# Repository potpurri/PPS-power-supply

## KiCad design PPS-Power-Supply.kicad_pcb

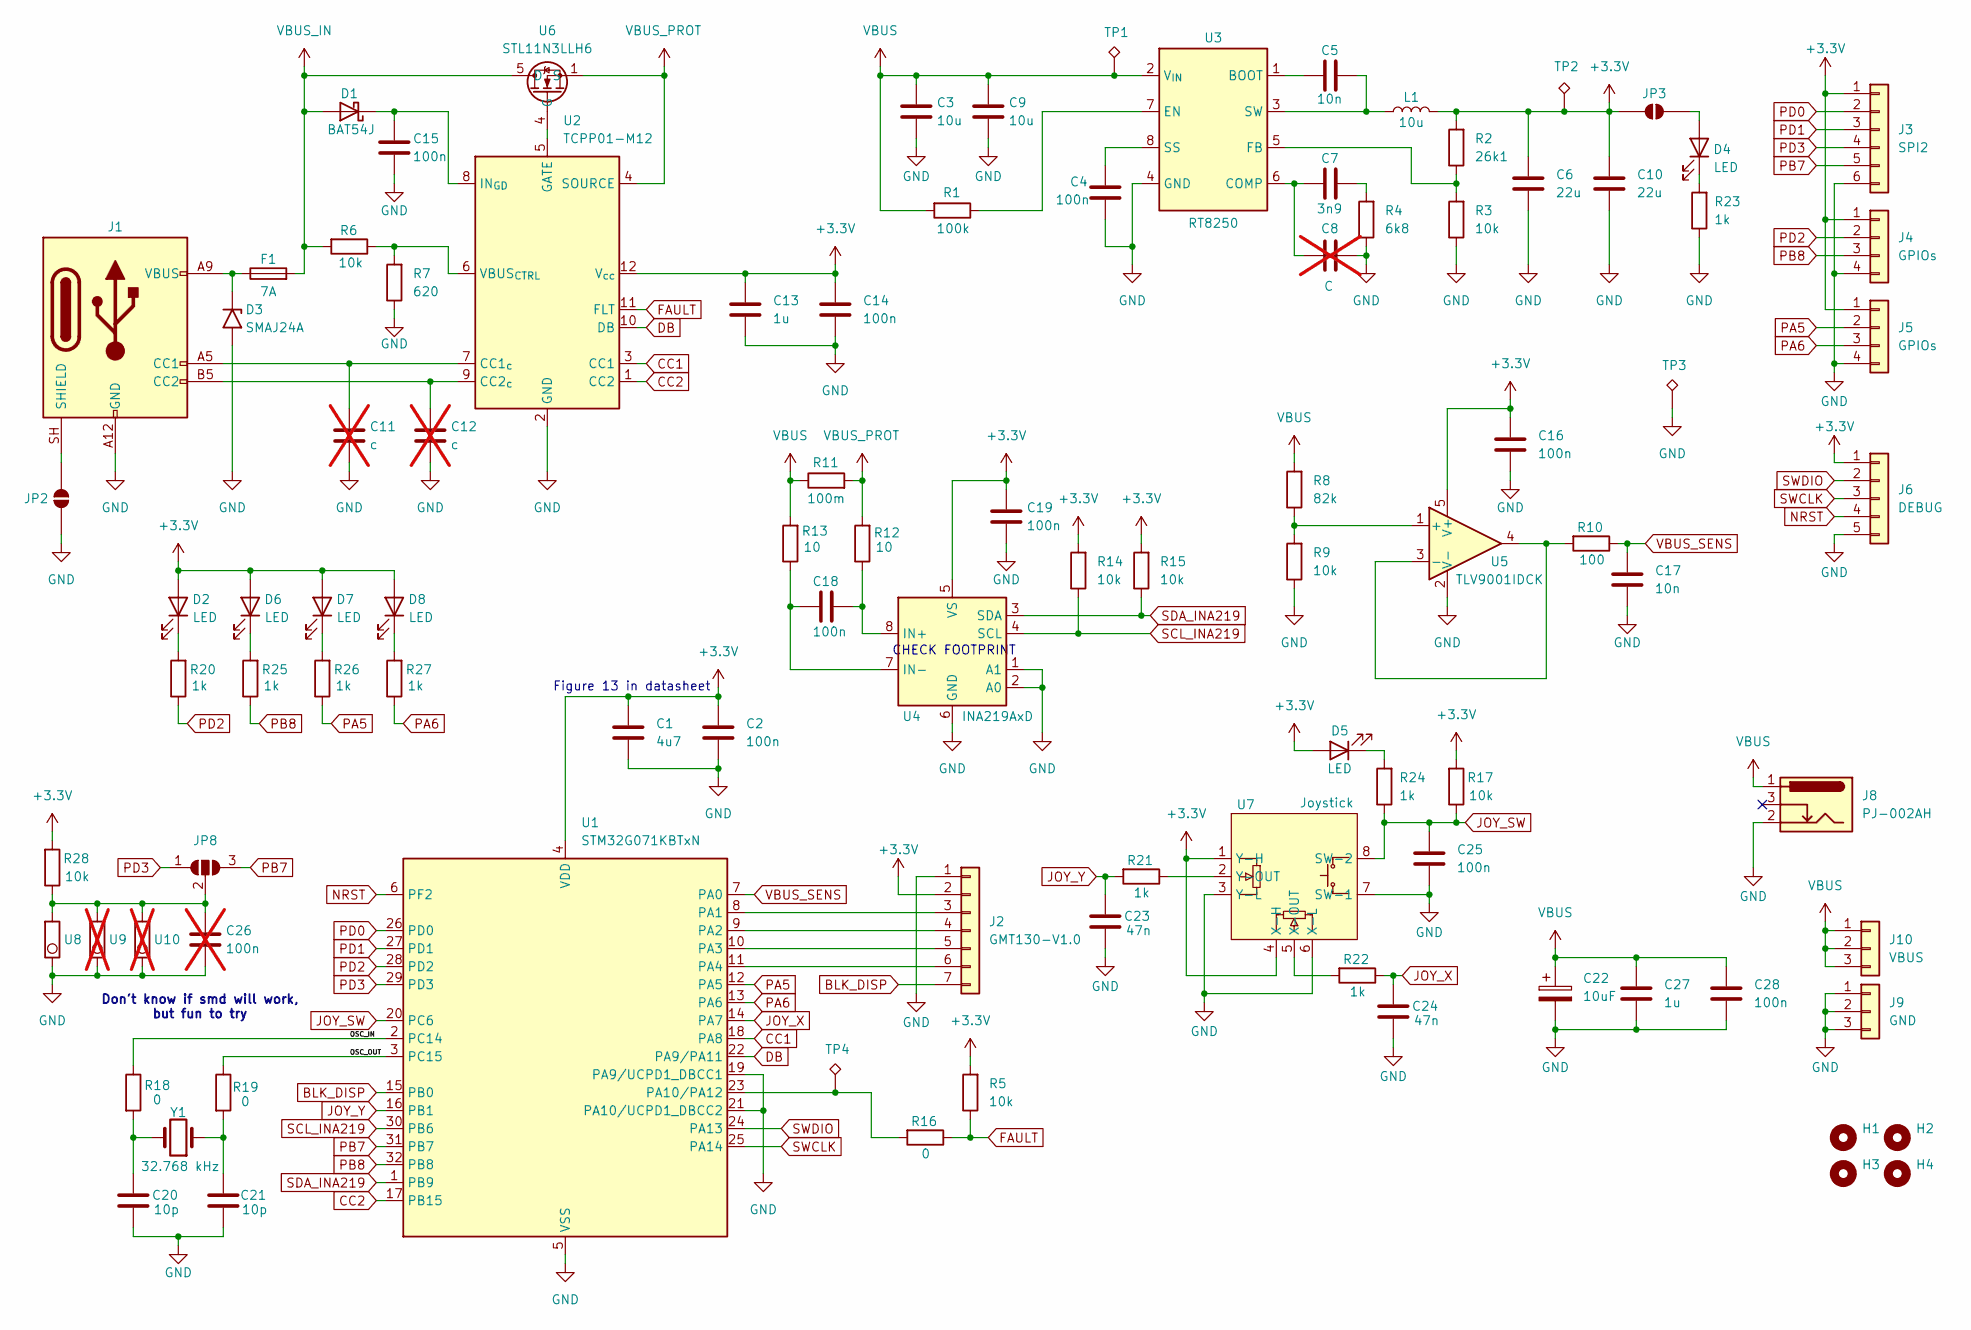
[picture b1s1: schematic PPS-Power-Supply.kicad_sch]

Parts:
C1: 4u7; C_0805_2012Metric
C2, C4, C14, C15, C16, C18, C19, C25, C28: 100n; C_0603_1608Metric
C3, C9: 10u; C_1206_3216Metric
C5, C17: 10n; C_0603_1608Metric
C6, C10: 22u; C_1206_3216Metric
C7: 3n9; C_0603_1608Metric
C8: C; C_0603_1608Metric; not fitted
C11, C12: c; C_0603_1608Metric; not fitted
C13, C27: 1u; C_0805_2012Metric
C20, C21: 10p; C_0603_1608Metric
C22: 10uF; CP_Elec_5x5.3
C23, C24: 47n; C_0603_1608Metric
C26: 100n; C_0603_1608Metric; not fitted
D1: BAT54J; D_SOD-323F
D2, D4, D5, D6, D7, D8: LED; LED_0805_2012Metric
D3: SMAJ24A; D_SMB
F1: 7A; Fuse_1206_3216Metric
H1, H2, H3, H4: MountingHole; MountingHole_3.2mm_M3_DIN965_Pad_TopBottom
J1: USB_C_Receptacle_PowerOnly_6P; USB_C_Receptacle_HRO_TYPE-C-31-M-17
J2: GMT130-V1.0; PinHeader_1x07_P2.54mm_Vertical
J3: SPI2; PinHeader_1x06_P2.54mm_Vertical
J4, J5: GPIOs; PinHeader_1x04_P2.54mm_Vertical
J6: DEBUG; PinHeader_1x05_P2.54mm_Vertical
J8: PJ-002AH; BarrelJack_GCT_DCJ200-10-A_Horizontal
J9: GND; PinHeader_1x03_P2.54mm_Vertical
J10: VBUS; PinHeader_1x03_P2.54mm_Vertical
JP2, JP3: SolderJumper_2_Open; SolderJumper-2_P1.3mm_Open_RoundedPad1.0x1.5mm
JP8: SolderJumper_3_Open; SolderJumper-3_P1.3mm_Open_RoundedPad1.0x1.5mm
L1: 10u; L_APV_ANR5020
R1: 100k; R_0603_1608Metric
R2: 26k1; R_0603_1608Metric
R3, R5, R6, R9, R14, R15, R17, R28: 10k; R_0603_1608Metric
R4: 6k8; R_0603_1608Metric
R7: 620; R_0603_1608Metric
R8: 82k; R_0603_1608Metric
R10: 100; R_0603_1608Metric
R11: 100m; R_2512_6332Metric
R12, R13: 10; R_0603_1608Metric
R16, R18, R19: 0; R_0805_2012Metric
R20, R21, R22, R23, R24, R25, R26, R27: 1k; R_0603_1608Metric
TP1, TP2, TP3, TP4: TestPoint_Alt; TestPoint_Pad_D1.0mm
U1: STM32G071KBTxN; LQFP-32_7x7mm_P0.8mm
U2: TCPP01-M12; QFN-12-1EP_3x3mm_P0.5mm_EP1.45x1.45mm
U3: RT8250; Texas_HSOP-8-1EP_3.9x4.9mm_P1.27mm
U4: INA219AxD; SOIC-8_3.9x4.9mm_P1.27mm
U5: TLV9001IDCK; SOT-353_SC-70-5
U6: STL11N3LLH6; POWERFLAT-3p3X3p3_STM
U7: Joystick
U8: R_Axial_DIN0411_L9.9mm_D3.6mm_P15.24mm_Horizontal
U9, U10: L_1210_3225Metric; not fitted
Y1: 32.768 kHz; Crystal_SMD_3215-2Pin_3.2x1.5mm

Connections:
+3.3V: C1.1, C2.1, C6.1, C10.1, C13.1, C14.1, C16.1, C19.1, D2.2 (A), D5.2 (A), D6.2 (A), D7.2 (A), D8.2 (A), J2.2, J3.1, J4.1, J5.1, J6.1, JP3.1 (A), L1.2, R2.2, R5.2, R14.2, R15.2, R17.2, R28.2, TP2.1 (1_1), U1.4 (VDD), U2.12 (V_{cc}), U4.5 (VS), U5.5 (V+), U7.1 (Y-H), U7.4 (X-H)
/OSC_IN: R18.1, U1.2 (PC14)
/OSC_OUT: R19.1, U1.3 (PC15)
BLK_DISP: J2.7, U1.15 (PB0)
CC1: U1.18 (PA8), U2.3 (CC1)
CC2: U1.17 (PB15), U2.1 (CC2)
DB: U1.22 (PA9/PA11), U2.10 (DB)
FAULT: R5.1, R16.1, U2.11 (FLT)
GND: C1.2, C2.2, C3.2, C4.2, C6.2, C8.2, C9.2, C10.2, C11.2, C12.2, C13.2, C14.2, C15.2, C16.2, C17.2, C19.2, C20.2, C21.2, C22.2, C23.2, C24.2, C25.2, C26.2, C27.2, C28.2, D3.2 (A2), J1.A12 (GND), J1.B12 (GND), J2.1, J3.6, J4.4, J5.4, J6.5, J8.2, J9.1, J9.2, J9.3, JP2.1 (A), R3.1, R4.1, R7.1, R9.1, R23.1, TP3.1 (1_1), U1.5 (VSS), U1.19 (PA9/UCPD1_DBCC1), U1.21 (PA10/UCPD1_DBCC2), U2.2 (GND), U2.13 (GND), U3.4 (GND), U3.9 (GND), U4.1 (A1), U4.2 (A0), U4.6 (GND), U5.2 (V-), U7.3 (Y-L), U7.6 (X-L), U7.7 (SW-1), U8., U8.1, U9., U9.1, U10., U10.1
JOY_SW: C25.1, R17.1, R24.1, U1.20 (PC6), U7.8 (SW-2)
JOY_X: C24.1, R22.1, U1.14 (PA7)
JOY_Y: C23.1, R21.2, U1.16 (PB1)
NRST: J6.4, U1.6 (PF2)
unnamed: C7.2, R4.2
unnamed: C20.1, R18.2, Y1.2
unnamed: C21.1, R19.2, Y1.1
unnamed: C15.1, D1.1 (K), U2.8 (IN_{GD})
unnamed: D2.1 (K), R20.2
unnamed: D3.1 (A1), F1.1, J1.A9 (VBUS), J1.B9 (VBUS)
unnamed: D4.2 (A), JP3.2 (B)
unnamed: D4.1 (K), R23.2
unnamed: D5.1 (K), R24.2
unnamed: D6.1 (K), R25.2
unnamed: D7.1 (K), R26.2
unnamed: D8.1 (K), R27.2
unnamed: C11.1, J1.A5 (CC1), U2.7 (CC1_{c})
unnamed: C12.1, J1.B5 (CC2), U2.9 (CC2_{c})
unnamed: J1.SH (SHIELD), JP2.2 (B)
unnamed: J2.3, U1.8 (PA1)
unnamed: J2.4, U1.9 (PA2)
unnamed: J2.5, U1.10 (PA3)
unnamed: J2.6, U1.11 (PA4)
unnamed: C26.1, JP8.2 (C), R28.1, U8., U8.2, U9., U9.2, U10., U10.2
unnamed: R16.2, TP4.1 (1_1), U1.23 (PA10/PA12)
unnamed: U2.5 (GATE), U6.4 (G)
unnamed: R6.1, R7.2, U2.6 (VBUS_{CTRL})
unnamed: C5.1, U3.1 (BOOT)
unnamed: C7.1, C8.1, U3.6 (COMP)
unnamed: R1.1, U3.7 (EN)
unnamed: R2.1, R3.2, U3.5 (FB)
unnamed: C4.1, U3.8 (SS)
unnamed: C5.2, L1.1, U3.3 (SW)
unnamed: C18.1, R12.1, U4.8 (IN+)
unnamed: C18.2, R13.1, U4.7 (IN-)
unnamed: R8.1, R9.2, U5.1 (+)
unnamed: R10.2, U5.3 (-), U5.4
unnamed: R22.2, U7.5 (X-OUT)
unnamed: R21.1, U7.2 (Y-OUT)
PA5: J5.2, R26.1, U1.12 (PA5)
PA6: J5.3, R27.1, U1.13 (PA6)
PB7: J3.5, JP8.3 (B), U1.31 (PB7)
PB8: J4.3, R25.1, U1.32 (PB8)
PD0: J3.2, U1.26 (PD0)
PD1: J3.3, U1.27 (PD1)
PD2: J4.2, R20.1, U1.28 (PD2)
PD3: J3.4, JP8.1 (A), U1.29 (PD3)
SCL_INA219: R14.1, U1.30 (PB6), U4.4 (SCL)
SDA_INA219: R15.1, U1.1 (PB9), U4.3 (SDA)
SWCLK: J6.3, U1.25 (PA14)
SWDIO: J6.2, U1.24 (PA13)
VBUS: C3.1, C9.1, C22.1, C27.1, C28.1, J8.1, J10.1, J10.2, J10.3, R1.2, R8.2, R11.1, R13.2, TP1.1 (1_1), U3.2 (V_{IN})
VBUS_IN: D1.2 (A), F1.2, R6.2, U6.5 (D), U6.6 (D), U6.7 (D), U6.8 (D)
VBUS_PROT: R11.2, R12.2, U2.4 (SOURCE), U6.1 (S), U6.2 (S), U6.3 (S)
VBUS_SENS: C17.1, R10.1, U1.7 (PA0)

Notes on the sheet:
Don't know if smd will work, but fun to try
CHECK FOOTPRINT
Figure 13 in datasheet

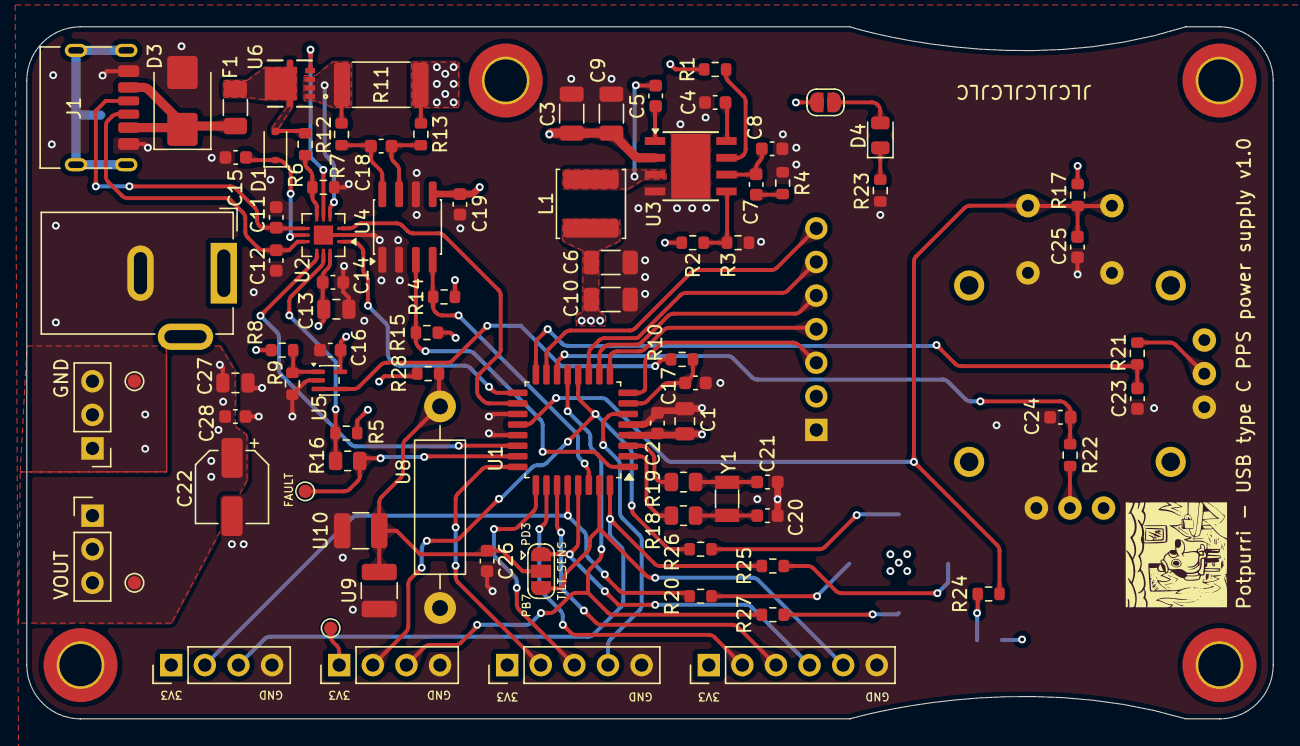
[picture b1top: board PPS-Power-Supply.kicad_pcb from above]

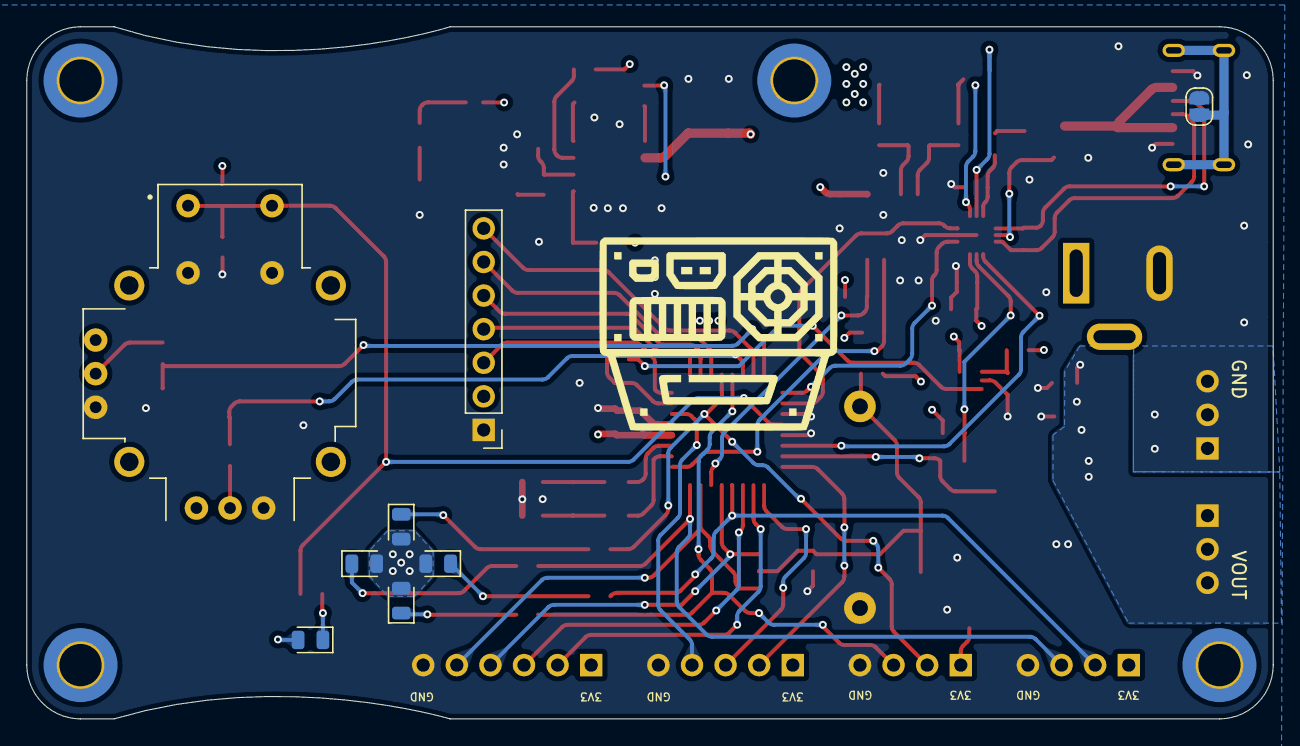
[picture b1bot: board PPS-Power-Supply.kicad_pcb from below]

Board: 4 copper layers, 94.2 x 52.3 mm, 97 parts (8 on the bottom side), 64 nets.

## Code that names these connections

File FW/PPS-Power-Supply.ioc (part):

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Mcu.Name=STM32G071K(8-B)TxN
Mcu.Package=LQFP32
Mcu.UserName=STM32G071KBTxN
PA0.GPIOParameters=GPIO_Label
PA0.GPIO_Label=VBUS_SENS
PA0.Mode=IN0
PA0.Signal=ADC1_IN0
PA1.GPIOParameters=GPIO_Label
PA1.GPIO_Label=SCK_DISP
PA1.Mode=Simplex_Bidirectional_Master
PA1.Signal=SPI1_SCK
PA10.Mode=EnableDeadBattery
PA10.Signal=UCPD1_DBCC2
PA11\ [PA9].GPIOParameters=PinState,GPIO_Label
PA11\ [PA9].GPIO_Label=DB
PA11\ [PA9].PinState=GPIO_PIN_SET
PA11\ [PA9].Signal=GPIO_Output
PA12\ [PA10].GPIOParameters=GPIO_Label
PA12\ [PA10].GPIO_Label=FLT
PA12\ [PA10].Signal=GPIO_Input
PA13.Mode=Serial_Wire
PA13.Signal=SYS_SWDIO
PA14-BOOT0.Mode=Serial_Wire
PA14-BOOT0.Signal=SYS_SWCLK
PA2.GPIOParameters=GPIO_Label
PA2.GPIO_Label=SDA_DISP
PA2.Mode=Simplex_Bidirectional_Master
PA2.Signal=SPI1_MOSI
PA3.GPIOParameters=GPIO_Label
PA3.GPIO_Label=RES_DISP
PA3.Signal=GPIO_Output
PA4.GPIOParameters=GPIO_Label
PA4.GPIO_Label=DC_DISP
PA4.Signal=GPIO_Output
PA7.GPIOParameters=GPIO_Label
PA7.GPIO_Label=JOY_X
PA7.Mode=IN7
PA7.Signal=ADC1_IN7
PA8.Mode=Sink_AllSignals
PA8.Signal=UCPD1_CC1
PA9.Mode=EnableDeadBattery
PA9.Signal=UCPD1_DBCC1
PB0.GPIOParameters=GPIO_Label
PB0.GPIO_Label=BLK_DISP
PB0.Signal=S_TIM3_CH3
PB1.GPIOParameters=GPIO_Label
PB1.GPIO_Label=JOY_Y
PB1.Mode=IN9
PB1.Signal=ADC1_IN9
PB15.Mode=Sink_AllSignals
PB15.Signal=UCPD1_CC2
PB6.GPIOParameters=GPIO_Label
PB6.GPIO_Label=SCL_INA219
PB6.Mode=I2C
PB6.Signal=I2C1_SCL
PB9.GPIOParameters=GPIO_Label
PB9.GPIO_Label=SDA_INA219
PB9.Mode=I2C
PB9.Signal=I2C1_SDA
PC14-OSC32_IN\ (PC14).GPIOParameters=GPIO_Label
PC14-OSC32_IN\ (PC14).GPIO_Label=OSC_IN
PC14-OSC32_IN\ (PC14).Mode=LSE-External-Oscillator
PC14-OSC32_IN\ (PC14).Signal=RCC_OSC32_IN
PC15-OSC32_OUT\ (PC15).GPIOParameters=GPIO_Label
PC15-OSC32_OUT\ (PC15).GPIO_Label=OSC_OUT
PC15-OSC32_OUT\ (PC15).Mode=LSE-External-Oscillator
PC15-OSC32_OUT\ (PC15).Signal=RCC_OSC32_OUT
PC6.GPIOParameters=GPIO_Label
PC6.GPIO_Label=JOY_SW
PC6.Signal=GPIO_Input
RCC.HSE_VALUE=8000000
RCC.SYSCLKFreq_VALUE=16000000
board=custom

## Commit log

2026-04-06 version 1.0
